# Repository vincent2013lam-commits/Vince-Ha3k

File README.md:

Starbie is an interactive electronic pet. It features a microcontroller, buttons, an Arduino code, and a custom design. The project consists with a Kicad schematic design, hosting all of the components, and a pcb design, where we construct and place all of the components. The code is in Aduino and in C++, featuring all of the starbie's responses and overall behavior.

Starbie Image:

(I may not add images)

First things, to make a Starbie, we need the following components:
- 0.96-inch OLED Display: Shows data from the Starbie Program

- XIAO ESP32 C3: Runs the Arduino code

- DHT11: Measures the air temperature and humidity

- MPU6050: Detects movement

- MX Switches: Allows pressing

- Keycaps: Allows pressing

- 10k Resistor: Controls electrical current

- PCB: The entire system the Starbie operates on

Bill of Materials Table:

Making the 5TARBIE process:
1. Sketch the needed components on the schematic editior
2. Transfer the schematic to the pcb editor
3. Wire every needed connection and design the base of your star
4. Use the Design Rules Checker to catch any mistakes

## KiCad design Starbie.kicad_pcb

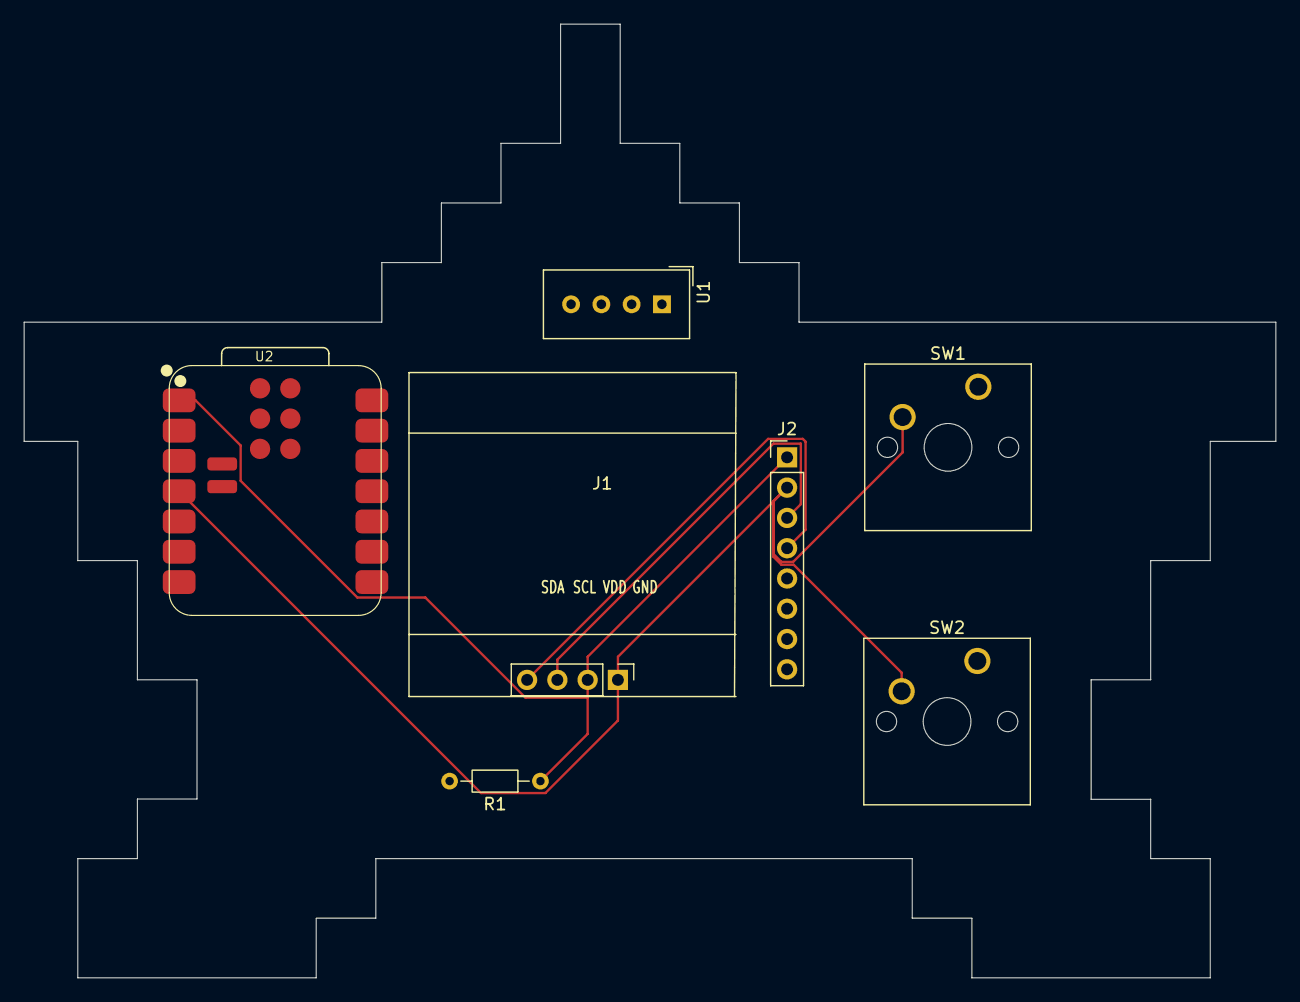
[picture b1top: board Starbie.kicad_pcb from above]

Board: 2 copper layers, 105.0 x 80.0 mm, 7 parts (0 on the bottom side), 5 nets.

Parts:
J1: Conn_01x04_Pin; Display_128x64_096_I2C
J2: Conn_01x08_Pin; PinHeader_1x08_P2.54mm_Vertical
R1: 10k; R_Axial_DIN0204_L3.6mm_D1.6mm_P7.62mm_Horizontal
SW1, SW2: SW_Push; SW_Cherry_MX_1.00u_PCB
U1: XIAO-ESP32-C3-SMD; Aosong_DHT11_5.5x12.0_P2.54mm
U2: DHT11; XIAO-ESP32-C3-SMD

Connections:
+3.3V: J1.2, J2.1, R1.1, U2.1 (VDD)
/DHT11 DATA: R1.2, U2.2 (DATA)
/SCL: J1.3, J2.3
/SDA: J1.4, J2.4
GND: J1.1, J2.2, SW1.2, SW2.2, U2.4 (GND)
